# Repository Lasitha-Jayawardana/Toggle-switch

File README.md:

# Toggle-switch
PCB design for Simple toggle switch using SMD 4017 IC . 

## Tips

  This PCB is design for On of Off toggle switch for small load (Ultra bright LED).
  This is a compress design to minimize dimensions.

  Protues and Eagle Cad projects files, Camoutputs and CNC milling files are herewith.

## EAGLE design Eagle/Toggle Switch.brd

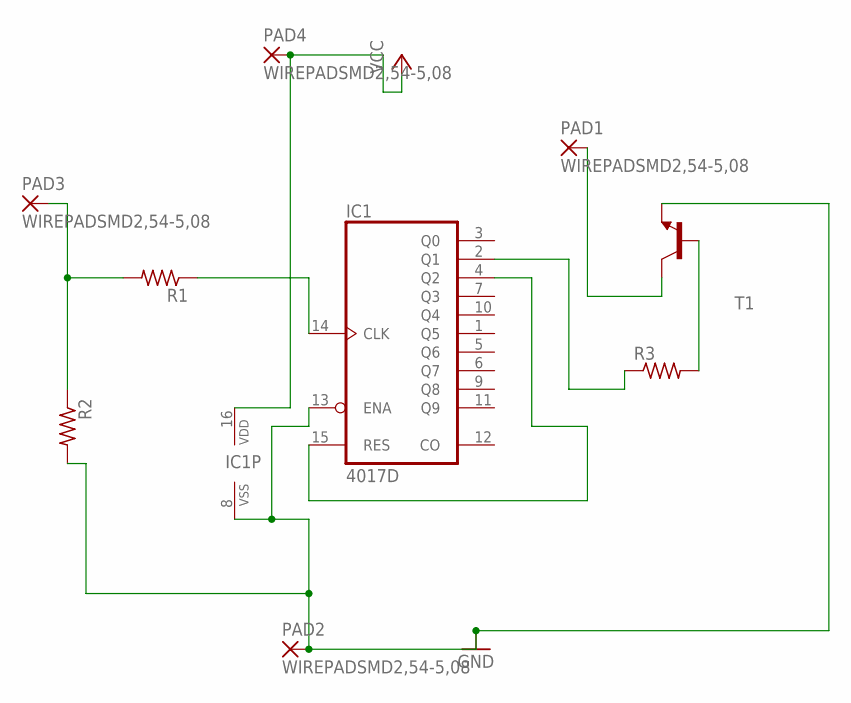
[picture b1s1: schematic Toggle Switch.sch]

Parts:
IC1: 4017D; SO16
PAD1, PAD2, PAD3, PAD4: WIREPADSMD2,54-5,08; SMD2,54-5,08
R1, R2, R3: R-US_0207/7; 0207/7
T1: BC639-NPN-TO92-ECB; TO92-ECB

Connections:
GND: IC1.8 (VSS), IC1.13 (ENA), PAD2.1, R2.2, T1.E
unnamed: IC1.14 (CLK), R1.1
unnamed: PAD3.1, R1.2, R2.1
unnamed: IC1.4 (Q2), IC1.15 (RES)
unnamed: IC1.2 (Q1), R3.1
unnamed: R3.2, T1.B
unnamed: PAD1.1, T1.C
VCC: IC1.16 (VDD), PAD4.1

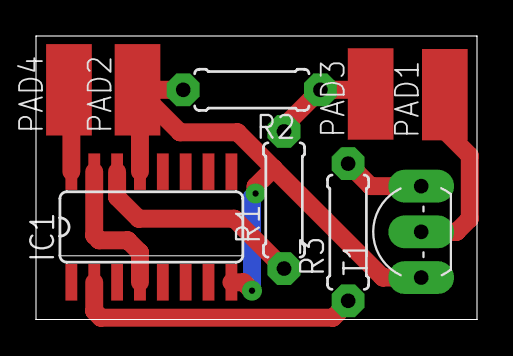
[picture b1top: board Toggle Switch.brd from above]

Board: 2 copper layers, 24.5 x 15.8 mm, 9 parts (0 on the bottom side), 8 nets.
